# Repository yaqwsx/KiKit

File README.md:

# KiKit – Automation for KiCAD

KiKit is a Python library, KiCAD plugin and  a CLI tool to automate several
tasks in a standard KiCAD workflow like:

- panelization of both, regular and oddly shaped, boards (see
  [examples](https://yaqwsx.github.io/KiKit/latest/panelization/examples/))
- automated exporting manufacturing data based on manufacturer presets
- multi-board project in KiCAD
- building board presentation pages (see [an example presentation page generated
  by KiKit](https://roboticsbrno.github.io/RB0002-BatteryPack))

## Do You Enjoy KiKit or Does It Save You Time?

Then definitely consider:

- [**supporting me on GitHub Sponsors**](https://github.com/sponsors/yaqwsx)
- or become my [Patreon](https://patreon.com/yaqwsx),
- or buy me a coffee: 

Your support will allow me to allocate time to properly maintain my projects
like this.

PS: Be sure to check out my other KiCAD & PCB related projects:

- [Pinion](https://github.com/yaqwsx/Pinion/)
- [PcbDraw](https://github.com/yaqwsx/PcbDraw/)
- [JlcParts](https://github.com/yaqwsx/jlcparts)

## Installation

KiKit is available as a [PyPi package](https://pypi.org/project/KiKit/).
However, due to packaging of KiCAD, installation on some platforms requires
usage of specific Python interpreter.

Please follow the detailed [installation
guide](https://yaqwsx.github.io/KiKit/latest/installation/intro/) that covers
installation based on the platform you use.

## Why Should I Use It?

Everything KiKit does, can also be done via Pcbnew in KiCAD. However, you have
to do it manually. One of the common scenarios is the creation of panels. Most
of the tutorials on the internet guide you to use the "append board"
functionality of Pcbnew. However, this approach is labour-intensive, error-prone
and whenever, you change the board, you have to do it again.

With KiKit you just call a CLI command if you have a simple layout (e.g., a
grid) or write few Python instructions like "place board here", "add bridge
here", "separate boards via mouse bites/v-cuts" and you are done. The process is
repeatable and actually much simpler than hand-drawing the panels. KiKit also
allows you to easily export all the Gerbers in a single step.

You can then write a Makefile and simply call `make` to get all your
manufacturing data and board presentation pages.

## Feature List

- create panels by appending boards and pieces of substrate (bridges)
- supports board with arbitrary shapes
- easily create mouse-bites/V-CUTS
- compared to hand-creation of panels, your panels will pass DRC (as tracks from
  different instances of the same board have distinct nets when using KiKit)
- if you have multiple boards in a single file, you can split them
- simplifying [multi-board project in KiCAD](https://yaqwsx.github.io/KiKit/latest/multiboard/)
- [automated export of gerbers and assembly data](https://yaqwsx.github.io/KiKit/latest/fabrication/intro/)
- [3D printed self-registering solder paste stencils](https://yaqwsx.github.io/KiKit/upstream/latest/stencil/#3d-printed-stencils)
- [steel stencils with alignment jig](https://yaqwsx.github.io/KiKit/latest/stencil/#steel-stencils)
- create powerfull shell scrips or Makefiles which automates your workflow...
- ...or invoke the functionality via [GUI in KiCAD](https://yaqwsx.github.io/KiKit/latest/panelization/gui/).

## How To Use It?

Start with reading the [panelization
documentation](https://yaqwsx.github.io/KiKit/latest/panelization/intro/). This
page will you guide through CLI, GUI and scripting usage. Also don't miss the
[examples](https://yaqwsx.github.io/KiKit/latest/panelization/examples/).
There is also a quick note on how to use [panelization action
plugin](https://yaqwsx.github.io/KiKit/latest/panelization/gui/). If you are
interested in generating solder paste stencils, see [Stencil
documentation](https://yaqwsx.github.io/KiKit/latest/stencil/)

## Acknowledgements

The project is supported by:

- [My GitHub sponsors](https://github.com/sponsors/yaqwsx) and
- 

## KiKit Is Broken or Does Not Work as Expected

Please, first check [FAQ](https://yaqwsx.github.io/KiKit/latest/faq/). If you have not found answer for your
problem there, feel free to open an issue on GitHub.

If you would like to have a feature in KiKit that is currently not on a roadmap,
or if you need to prepare custom panelization script (e.g., multi-design panels,
panels with specific arrangement), you can consider hiring me to do the job.
Just reach out to me via e-mail and we can discuss further details.

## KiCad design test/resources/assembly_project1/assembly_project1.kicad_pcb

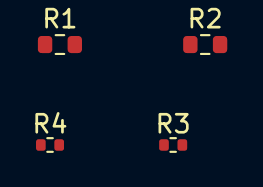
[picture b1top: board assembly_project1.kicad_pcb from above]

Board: 2 copper layers, 4 parts (0 on the bottom side), 2 nets, no tracks yet.

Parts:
R1: R1_VAL; R_0603_1608Metric
R2: R2_VAL; R_0603_1608Metric
R3, R4: R3/R4_VAL; R_0402_1005Metric

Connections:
/Nested sheet/C: R1.2, R2.1, R3.1, R4.1
/Nested sheet/D: R1.1, R2.2, R3.2, R4.2

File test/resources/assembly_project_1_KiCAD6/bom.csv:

Comment,Designator,Footprint,LCSC
R1_VAL,R1,Resistor_SMD:R_0603_1608Metric,LCSC_R1
R2_VAL,R2,Resistor_SMD:R_0603_1608Metric,LCSC_R2
R3/R4_VAL,"R3,R4",Resistor_SMD:R_0402_1005Metric,LCSC_R3/R4

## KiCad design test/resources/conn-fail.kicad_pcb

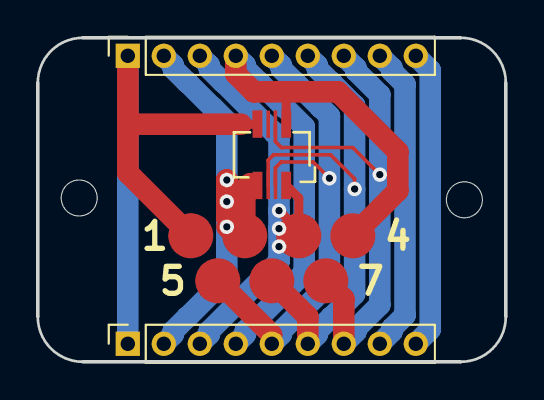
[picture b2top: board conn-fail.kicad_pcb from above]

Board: 2 copper layers, 26.0 x 18.0 mm, 6 parts (0 on the bottom side), 9 nets.

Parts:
H1, H2: MountingHole; MountingHole_2mm
J1: IN; PinSocket_1x09_P2.00mm_Vertical
J2: OUT; PinSocket_1x09_P2.00mm_Vertical
J3: POGO; pogo_pads_4_3
J4: Molex; molex-505004-0812

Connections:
1: J1.1, J2.1, J3.1, J4.8
2: J1.2, J2.2, J3.2, J4.7
3: J1.3, J2.3, J3.3, J4.1
4: J1.4, J2.4, J3.4, J4.2
5: J1.5, J2.5, J3.5, J4.3
6: J1.6, J2.6, J3.6, J4.5
7: J1.7, J2.7, J3.7, J4.4
8: J1.8, J2.8
9: J1.9, J2.9

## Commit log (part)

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2024-01-06 Implement support for fab openpn
2024-01-06 Deployed db18615 to upstream with MkDocs 1.5.3 and mike 2.0.0
2024-01-31 Inherit layer names
2024-02-06 Introduce compatibility with KiCAD v8
2024-02-06 Adapt tests to KiCAD 8
2024-02-06 Allow for alternative PYTHON paths for nightly
2024-02-06 Properly extract annotations for v8
2024-02-06 Deployed 0cfe557 to upstream with MkDocs 1.5.3 and mike 2.0.0
2024-02-06 Deployed b3cb8d5 to upstream with MkDocs 1.5.3 and mike 2.0.0
2024-02-09 Generalize run_with_debug
2024-02-09 Descrese the tolarance
2024-02-09 Fix board comments by properly capturing comment index in lambda
2024-02-13 Add 'solderMaskMargin' parameter to Tooling
2024-02-15 Add documentation for new solderMaskMargin arg for Panel.addNPTHole()
2024-02-15 Deployed a49b818 to upstream with MkDocs 1.5.3 and mike 2.0.0
2024-02-15 Deployed e0a347a to upstream with MkDocs 1.5.3 and mike 2.0.0
2024-02-20 Deployed 6279b0e to upstream with MkDocs 1.5.3 and mike 2.0.0
2024-02-21 Deployed 970db7a to upstream with MkDocs 1.5.3 and mike 2.0.0
2024-02-21 Deployed 8855237 to upstream with MkDocs 1.5.3 and mike 2.0.0
2024-02-21 Fix handling of DNP in JLC PCB fab
2024-02-21 Be clear about installation in README
2024-02-24 Do not use removed API in KiCAD 8
2024-02-24 Deployed 69262aa to upstream with MkDocs 1.5.3 and mike 2.0.0
2024-02-24 Deployed 8e0fcb8 to upstream with MkDocs 1.5.3 and mike 2.0.0
2024-02-26 Deployed 63883b3 to upstream with MkDocs 1.5.3 and mike 2.0.0
2024-02-26 Update CI to use KiCAD 8
2024-02-26 Do not yield zero-length segments
2024-02-26 Release v1.5.0
2024-02-26 Deployed 14f74e8 to v1.5 with MkDocs 1.5.3 and mike 2.0.0
2024-02-29 Do not test nightly as it already contains breaking changes
2024-03-06 Deployed a2c9891 to upstream with MkDocs 1.5.3 and mike 2.0.0
2024-03-06 Introduce a new arcwelder
2024-03-07 Fix arc welder for v7
2024-03-07 Be more tolerant in preserving slots
2024-03-07 Update issue template
2024-03-10 Add tests for DRC exclusion
2024-03-10 Fixed `OddEvenRowsColumnsPosition`. Added tests for placers `.rotation()`.
2024-03-10 Fix `test_basic_grid_position_rotation`
2024-03-10 Deployed 28689df to upstream with MkDocs 1.5.3 and mike 2.0.0
2024-03-10 Be more verbose in DRC tests
2024-03-10 Correctly handle footprint_type_mismatch DRC exclusion
2024-03-10 Clarify imortance of steps to reproduce in the issue template
2024-03-10 Update DRC test resource
2024-03-10 Deployed 0635768 to upstream with MkDocs 1.5.3 and mike 2.0.0
2024-03-11 Fix links in README
2024-03-13 Use simpler approach for preserving orientation of the text
2024-03-13 docs/panelization/examples: get rid of quotes in quotes
2024-03-15 Deployed 0dab911 to upstream with MkDocs 1.5.3 and mike 2.0.0
2024-03-15 Deployed 077c8ab to upstream with MkDocs 1.5.3 and mike 2.0.0
2024-03-16 Update Docker images to CI
2024-03-16 Bump pcbnewTransition dependency
2024-03-16 Deployed 897231d to upstream with MkDocs 1.5.3 and mike 2.0.0
2024-03-16 Deployed 7a3ae34 to upstream with MkDocs 1.5.3 and mike 2.0.0
2024-03-16 Add proper attributes to footprints
2024-03-16 Deployed 6bff8c2 to upstream with MkDocs 1.5.3 and mike 2.0.0
2024-03-17 Introduce error annotations
2024-03-17 Add option to specify the rendered width of the line
2024-03-17 Add option to fine-tweak V-cuts
2024-03-22 Change output handling in GUI
2024-03-26 Add an option to entirely skip components with missing LCSC field
    This is useful since JLCPCB tries to be "smart" and assign
    (wrong or unneeded) components even when the LCSC field is empty in
    the BoM.
2024-04-09 Deployed 11ce2b3 to upstream with MkDocs 1.5.3 and mike 2.0.0
2024-04-17 Fix V-cuts fine tune options
2024-04-17 Do not yield false tiny arcs
2024-04-27 VCUT Comments Layer
2024-05-02 Deployed 551e670 to upstream with MkDocs 1.6.0 and mike 2.1.0
2024-05-03 Deployed e0c312a to upstream with MkDocs 1.6.0 and mike 2.1.0
2024-05-07 Deployed 3636a3e to upstream with MkDocs 1.6.0 and mike 2.1.1
2024-05-12 Make edge geometry validity consistent with ring extraction
2024-05-13 Deployed f95fa41 to upstream with MkDocs 1.6.0 and mike 2.1.1
2024-05-15 Update fab settings for JLCPCB
    Per this article: https://jlcpcb.com/help/article/362-how-to-generate-gerber-and-drill-files-in-kicad-7
    * Drill files: Don't merge PTH and NPTH
    * Drill map files: Gerber format instead of PDF
2024-05-15 Deployed 32187ad to upstream with MkDocs 1.6.0 and mike 2.1.1
2024-05-19 Deployed 319f1d0 to upstream with MkDocs 1.6.0 and mike 2.1.1
2024-05-22 Add missing options to GUI
2024-05-22 Deployed cc6f4dc to upstream with MkDocs 1.6.0 and mike 2.1.1
2024-05-23 Fix formatting
2024-06-04 Deployed 0b6917b to upstream with MkDocs 1.6.0 and mike 2.1.1
2024-06-11 Remove forgotten debug trace
2024-06-12 Increase milling tolerance to accomodate for edge cases
2024-06-21 Fix UI check for output file
2024-06-21 Do not relay on cloud services to provide jig files
2024-06-22 Warn user if they didn't specify annotation reference
2024-06-28 Fix numpy imports
2024-06-28 Handle correction offsets and rotation separately
2024-07-15 Deployed 69bcf0b to upstream with MkDocs 1.6.0 and mike 2.1.2
2024-07-18 Deployed 7ce61d3 to upstream with MkDocs 1.6.0 and mike 2.1.2
2024-07-18 Make degenerated beziers compatible with shapely
2024-07-18 Fix text on bottom side for Windows
2024-07-18 Deployed 1f34883 to upstream with MkDocs 1.6.0 and mike 2.1.2
2024-07-18 Bump version
2024-07-23 Handle closed polygons well in substrate
2024-08-06 Introduce limit on arc size
2024-08-06 Deployed 31dcf01 to upstream with MkDocs 1.6.0 and mike 2.1.2
2024-08-15 Deployed ec75c91 to upstream with MkDocs 1.6.0 and mike 2.1.3
2024-09-15 Deployed a8d1c05 to upstream with MkDocs 1.6.1 and mike 2.1.3
2024-09-29 Deployed 571be59 to upstream with MkDocs 1.6.1 and mike 2.1.3
2024-10-11 Deployed 46b2ea9 to upstream with MkDocs 1.6.1 and mike 2.1.3
2024-10-29 Do not refill zones if there are none to refill
2024-10-29 Rework interaction with KiCAD's GUI
2024-10-29 Deployed 0330d8c to upstream with MkDocs 1.6.1 and mike 2.1.3
2024-11-04 Do not treat text as PCB outline
2024-11-07 Update GH actions
2024-11-12 Fix error reporting on V-cutting a curve
2024-11-12 Handle newlines in error reports properly
2024-11-21 For JLCPCB, flip orientation (incl. compensation angle) for bottom parts
    Fixes #664
2024-11-27 At least on KiCad 8.0.6 we can't just modify GetPosition() returned value
    Not at least adding a VECTORI2, so we need a copy.
    Adding (0, 0) does the work.
    Seen with text objects.
2025-01-25 Start working on a partition line
2025-01-26 Deployed b6a00ba to upstream with MkDocs 1.6.1 and mike 2.1.3
2025-01-26 Deployed ac2ef97 to upstream with MkDocs 1.6.1 and mike 2.1.3
2025-01-26 Fix wrong tooltips
2025-01-26 Update JLC PCB footprint orientation handling
2025-01-26 Add support for auto naming of JLC PCB fabrication
2025-01-26 Add co-option to JLC PCB assembly so we can switch to different default in the future
2025-01-29 Separate vertial and horizontal frame width
2025-02-06 Add Origin.AsSource
    Allows the original origin to be preserved. Useful for people who panelising boards that have strict coordinate systems from imported outlines from MCAD software.
2025-02-18 Deployed f3093fb to upstream with MkDocs 1.6.1 and mike 2.1.3
2025-02-24 Update CI to use the released KiCAD 9
2025-02-24 Deployed aa4eca3 to upstream with MkDocs 1.6.1 and mike 2.1.3
2025-02-24 Do not fail if there are no custom DRC rules
2025-02-24 Bump PCM version
2025-02-28 Adapt gerber export to the new layer numbering
2025-02-28 Check panel filename
2025-03-09 Make cuts corresponding to all substrates
2025-03-25 fix: LayerV2.all() returning nonexistent layers
2025-03-28 Deployed 6898f39 to upstream with MkDocs 1.6.1 and mike 2.1.3
2025-04-01 Deployed ecfa659 to upstream with MkDocs 1.6.1 and mike 2.1.3
2025-04-01 Bump version to v1.7.2
2025-04-02 Further optimize SExpr parser
2025-04-17 Improve error message when board doesn't exist
2025-04-17 Deployed 82b8409 to upstream with MkDocs 1.6.1 and mike 2.1.3
2025-04-27 Update windows.md with troubleshooting instructions
    The batch script that initializes paths in the command prompt enumerates existing directories only. Some plugin and script paths are only created after pip installs files that need to belong there. T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
2025-04-30 Fix jlcTooling preset
    The preset didn't have any effect because "type" was misspelled as "style".
2025-05-01 Resolve test name conflict of odd/even position rotation tests
2025-05-15 Implement odd/even grid offsets
2025-05-17 Display reference on error
2025-05-18 Deployed 559d637 to upstream with MkDocs 1.6.1 and mike 2.1.3
2025-06-22 Deployed f6932fa to upstream with MkDocs 1.6.1 and mike 2.1.3
2025-07-03 Deployed 1edfba0 to upstream with MkDocs 1.6.1 and mike 2.1.3
2025-07-23 resolves #801
2025-08-05 Allow to specify layer for annotation source
2025-08-18 Deployed 8c6643c to upstream with MkDocs 1.6.1 and mike 2.1.3
2025-08-18 Fix tooling.solderMaskMargin
    Fixes #689
2025-09-16 Deployed 3e321b2 to upstream with MkDocs 1.6.1 and mike 2.1.3
2025-09-16 Deployed 0a05942 to upstream with MkDocs 1.6.1 and mike 2.1.3
2025-09-20 CI: Test on the range of supported Python versions
    I wanted to make a change, but was worried about breaking things for older
    Pythons, so let's adjust CI to test on all supported versions (setup.py
    says `python_requires='>=3.7'`), so I can be confident in the changes.
    You know, what CI is for.
    Ideally, this would just be adding a dimension to the matrix and adding
    a call to `actions/setup-python`. Well, turns out:
2025-09-21 Add `make venv`
    I had a lot of trouble figuring out how to set up a nice contained
    development environment, so I figured I'd record it for others.
2025-10-12 Deployed b4f2692 to upstream with MkDocs 1.6.1 and mike 2.1.3
2025-10-25 Upgrade to modern Python packaging standards
    I guess this needs to be done by the end of next month:
    $ make package
    rm -f dist/*
    python3 setup.py sdist bdist_wheel
    /home/lukeshu/src/github.com/yaqwsx/KiKit/venv/lib/python3.13/site-packages/setuptools/__init__.py:92: _DeprecatedInstaller: setuptools.installer and fetch_build_eggs are deprecated.
    !!
2025-11-06 Deployed 6043817 to upstream with MkDocs 1.6.1 and mike 2.1.3
2025-11-14 Deployed ab63ca4 to upstream with MkDocs 1.6.1 and mike 2.1.3
2025-11-26 Add defaults
2026-01-26 KiCAD 10 updates: board.ResolveItem, zone.SetDoNotAllowZoneFills, self.substrates as GeometryCollection
2026-02-05 Build V9 docker images
2026-02-05 Fix suffix
2026-03-06 Copy/rename netclass_assignments from source board
2026-03-06 Accept empty netclass_assignments
2026-03-23 Support exposing arbitrary props from TabAnnotation init
2026-03-24 substrate: Support KiCad 10 native rounded rectangles
2026-03-27 Deployed 8f3e7f3 to upstream with MkDocs 1.6.1 and mike 2.1.4
2026-04-03 fix: KiCad 10 API compatibility in drc.py and panelize.py
    KiCad 10 introduced several breaking Python API changes that caused
    KiKit to crash when used with the new version:
    1. BOARD.GetItem(KIID) was renamed to BOARD.ResolveItem(KIID, allowNull).
    Fixed in drc.deserializeExclusion() and panelize.appendBoard() using
    a hasattr() shim so both old and new KiCad versions are supported.
    2. BOARD_ITEM.GetSelectMenuText() was removed in KiCad 10.
2026-04-06 Introduce KiCAD v10 support
    We drop the problematic pcbnewTransition
    dependency. We only support the 2 latest KiCAD
    versions, which are v10 and v9. Their API is
    mostly compatible, so we can support both easily
    without monkeypatching. As there won't be any v11
    SWIG API in KiCAD, this makes the codebase
2026-04-06 Update test files to v9
2026-04-06 Bump GH action files
2026-04-06 Update the PCM package
2026-04-06 Deployed 37621df to upstream with MkDocs 1.6.1 and mike 2.1.4
2026-04-06 Fix documentation link
2026-04-06 Make sure that newly added layers are enabled
2026-04-07 Fix building Docker images with newer Ubuntu base images
2026-04-07 Update dependencies in the Docker image
2026-04-07 Bump KiCAD version in dockerfile
2026-04-07 Improve doc on the corrections
2026-04-07 Deployed e010944 to upstream with MkDocs 1.6.1 and mike 2.1.4
2026-04-12 Deployed c0ea8ad to upstream with MkDocs 1.6.1 and mike 2.1.4
2026-04-12 Deployed 96eed3d to upstream with MkDocs 1.6.1 and mike 2.1.4
2026-04-12 Change strategy for filling full tabs
2026-04-17 Fix full tabs removing cutouts
2026-04-23 Deployed 6eb4e7a to v1.8 with MkDocs 1.6.1 and mike 2.2.0
